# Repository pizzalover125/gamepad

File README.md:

# gamepad
a gamepad designed to be as cheap as possible.

## Images

## BOM
* 8x 6mm buttons (FREE from cardPad)
* AliExpress Waveshare RP2040 Zero ($1.08)
* PCBs from PCBWay ($19.39)

**Total: $20.47**

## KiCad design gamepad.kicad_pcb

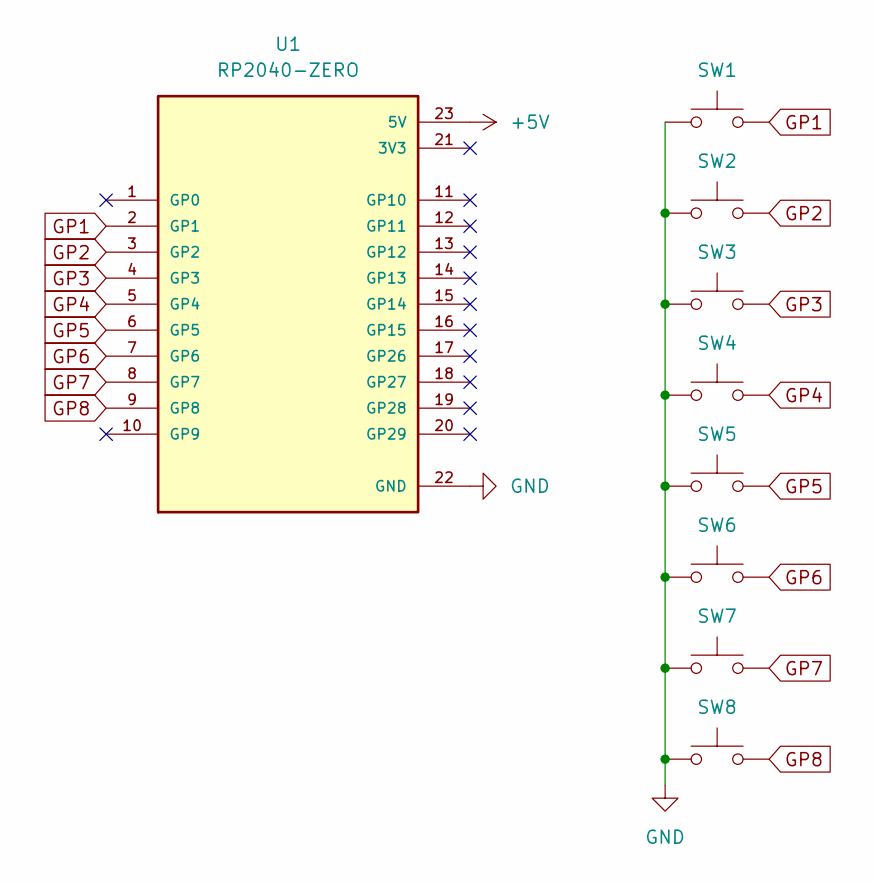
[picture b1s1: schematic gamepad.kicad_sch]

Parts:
SW1, SW2, SW3, SW4, SW5, SW6, SW7, SW8: SW_Push; SW_PUSH_6mm_H4.3mm
U1: RP2040-ZERO; MODULE_RP2040-ZERO; PARTREV NA

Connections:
+5V: U1.23 (5V)
GND: SW1.1, SW2.1, SW3.1, SW4.1, SW5.1, SW6.1, SW7.1, SW8.1, U1.22 (GND)
GP1: SW1.2, U1.2 (GP1)
GP2: SW2.2, U1.3 (GP2)
GP3: SW3.2, U1.4 (GP3)
GP4: SW4.2, U1.5 (GP4)
GP5: SW5.2, U1.6 (GP5)
GP6: SW6.2, U1.7 (GP6)
GP7: SW7.2, U1.8 (GP7)
GP8: SW8.2, U1.9 (GP8)

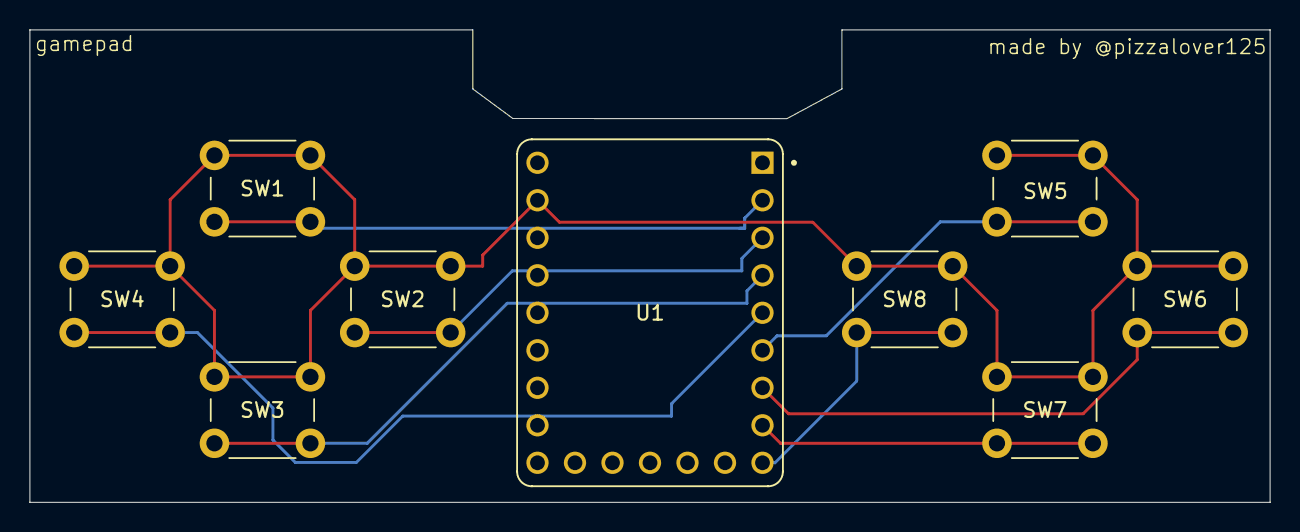
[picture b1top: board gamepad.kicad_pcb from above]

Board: 2 copper layers, 84.0 x 32.0 mm, 9 parts (0 on the bottom side), 9 nets.
